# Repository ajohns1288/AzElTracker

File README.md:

# AzElTracker
Arduino firmware to control https://www.thingiverse.com/thing:4664558, designed by jbyrns

This project started as a class project and was designed to be compatible (enough) to work with gPredict/rotctrld. It seems to run pretty well.

## Items Needed
1x Arduino Nano or equivalent

2x A4988 Stepper Boards

2x Stepper Motors

1x Small Magnet

1x Hall effect switch

## How it works
1: At startup, the azimuth is assumed to be due north (0deg) and the elevation runs a homing routine

2: Once homed, serial port is polled for commands from external program.

3: Rotors can be moved indepentently as well as together. Each can rotate continously or to a set position.

See section below for implemented commands

## Hardware adaptation

Since different people might want to use the same logic but for different hardware, the hardware specific values are in the rotorParams.h file. This way, you can tailor the code to your specific application without having to change mulitple variables all over the place

## Commands
Command enumerations based on GS232 Protocol; works with 'rotctld -m 606 -r /dev/xxx' on RaspPi

CMD_R 'R' - Move right continously

CMD_L 'L' - Move left continously

CMD_U 'U' - Move up continously

CMD_D 'D' - Move down continously

CMD_STOP 'S' - Stop all axes

CMD_STOP_AZ 'A' - Stop azimuth only

CMD_STOP_EL 'E' - Stop elevation only

CMD_SPEED 'X' - Xs - Set speed to x (Azimuth only, 4: fast 1: slow)

CMD_MOVETO_AZ 'M' - Mxxx  - Moves to azimuth xxx

CMD_MOVETO 'W' - Wxxx yyy - Moves to azimuth xxx, elevation yyy

CMD_GET_AZ 'C' - Display azimuth position only (NOTE: C2 will display both axes)

CMD_GET_EL 'B' - Display elevation position only

//Non-Standard GS232 Commands

CMD_DEBUG 'Q' - Displays current positions/status/modes of rotor

CMD_SET_HOME 'F' - Unimplmented, may be used to set current position as home in future release

## Drawbacks
Stepper motors do not have feedback. If the motor stalls or skips, your position will be off

## Future Work
Implement compass/accelerometer as position sensor input.

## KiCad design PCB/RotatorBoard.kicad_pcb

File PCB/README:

KiCad files for control board PCB

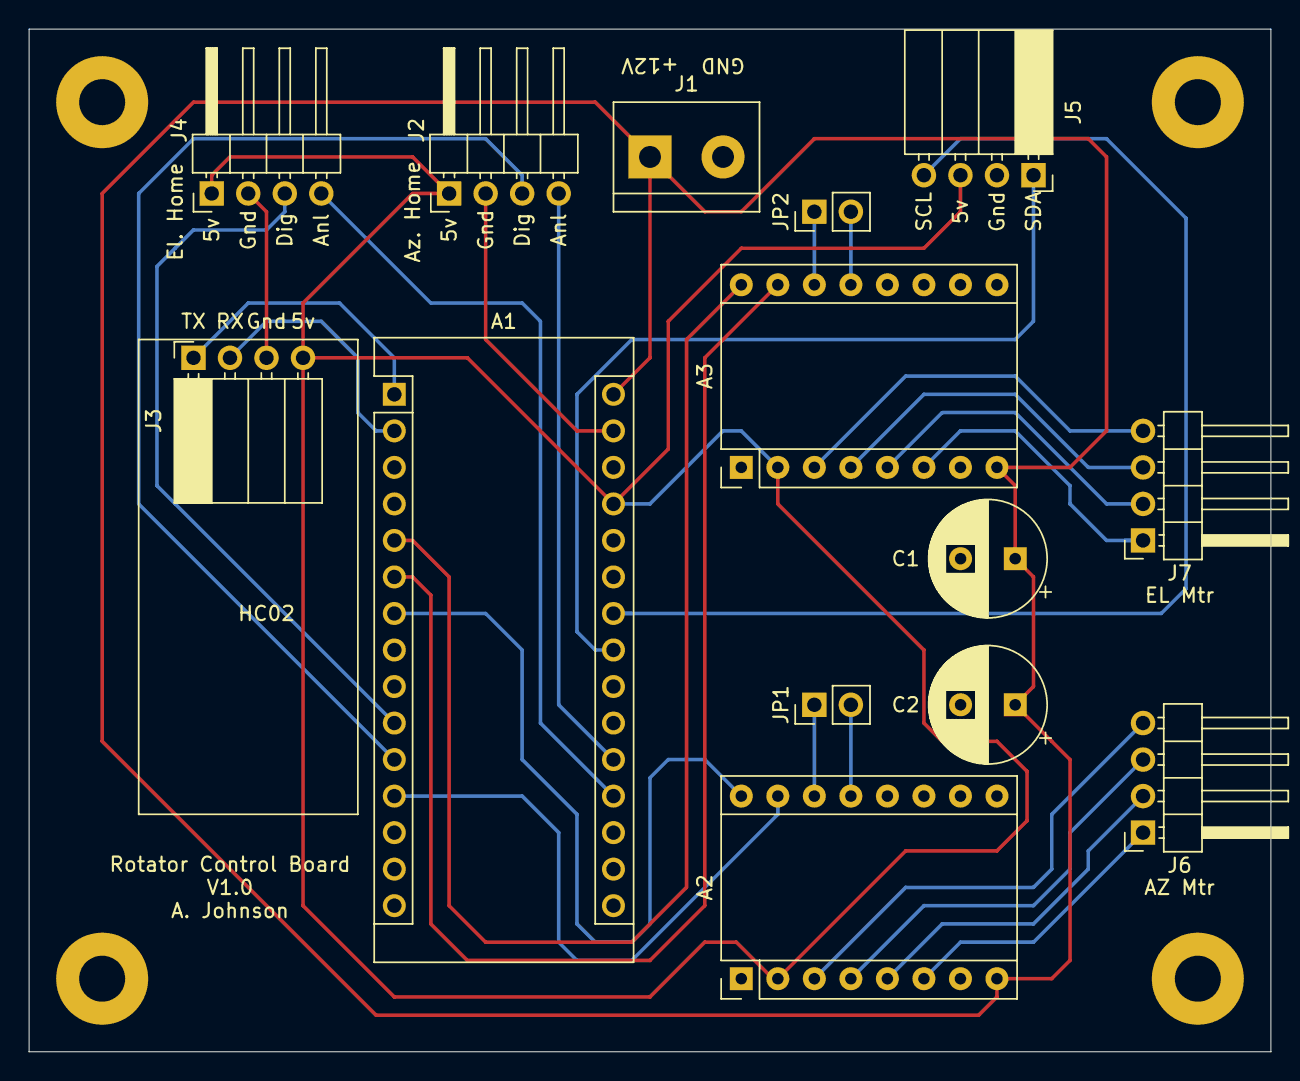
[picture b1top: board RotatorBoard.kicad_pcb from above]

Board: 2 copper layers, 86.4 x 71.1 mm, 14 parts (0 on the bottom side), 27 nets.

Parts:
A1: Arduino_Nano_v3.x; Arduino_Nano
A2, A3: Pololu_Breakout_A4988; Pololu_Breakout-16_15.2x20.3mm
C1, C2: CP1; CP_Radial_D8.0mm_P3.80mm
J1: Screw_Terminal_01x02; TerminalBlock_bornier-2_P5.08mm
J2, J4: Conn_01x04_Male; PinHeader_1x04_P2.54mm_Horizontal
J3, J5: Conn_01x04_Female; PinSocket_1x04_P2.54mm_Horizontal
J6, J7: Conn_01x04_Male; PinHeader_1x04_P2.54mm_HorizontalFlipped
JP1, JP2: Jumper_2_Open; PinHeader_1x02_P2.54mm_Vertical

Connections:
+5V: A1.27, A2.2, A3.2, J2.1, J3.4, J4.1, J5.3
+12V: A1.30, A2.8, A3.8, C1.1, C2.1, J1.1
AZ_DIR: A1.7, A2.16
AZ_HOME_ANL: A1.20, J2.4
AZ_HOME_DIG: A1.11, J2.3
AZ_STEP: A1.12, A2.15
EL_DIR: A1.5, A3.16
EL_HOME_ANL: A1.19, J4.4
EL_HOME_DIG: A1.10, J4.3
EL_STEP: A1.6, A3.15
GND: A1.4, A1.29, A2.1, A2.7, A3.1, A3.7, C1.2, C2.2, J1.2, J2.2, J3.3, J4.2, J5.2
I2C_SCL: A1.24, J5.4
I2C_SDA: A1.23, J5.1
unnamed: A2.3, J6.4
unnamed: A2.4, J6.3
unnamed: A2.5, J6.2
unnamed: A2.6, J6.1
unnamed: A2.13, JP1.2
unnamed: A2.14, JP1.1
unnamed: A3.3, J7.4
unnamed: A3.4, J7.3
unnamed: A3.5, J7.2
unnamed: A3.6, J7.1
unnamed: A3.13, JP2.2
unnamed: A3.14, JP2.1
UART_RX: A1.2, J3.2
UART_TX: A1.1, J3.1

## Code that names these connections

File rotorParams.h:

/*
 * These are the only things you should have to change for using it on your own design
 *
 * To determine the degrees per step, take the degrees per step for the motor (usually 1.8 degrees for a 200 step/rev
 * motor) and multiply it by the gear ratio. In my case, it was 1.8*(1/4.1) which gives 0.43 steps per degree.
 * To avoid floats, the code uses hundredths of degrees (ie 1 degree would be 100).
 */

#ifndef _ROTORPARAM_H
#define _ROTORPARAM_H

//Change these to match your specific rotor/steppers
//To avoid floats this is in 100th of a degree (deg*100)
#define AZ_DEG_PER_STEP 43 //(deg*100)
#define EL_DEG_PER_STEP 6 //(deg*100)

//Currently not used, however this is simply 1/(x/100) of the above
#define AZ_STEPS_PER_DEG 2.389
#define EL_STEPS_PER_DEG 16.66



//Change these to match your electrical setup
#define AZ_STEP_PIN 9
#define AZ_DIR_PIN 4

#define EL_STEP_PIN 3
#define EL_DIR_PIN 2

#define EL_HOME_PIN_DIG 7 //Digital home pin
#define EL_HOME_PIN_ANL A0 //Analog home pin

#define AZ_HOME_PIN_DIG 8  //Digital home pin
#define AZ_HOME_PIN_ANL A1 //Analog home pin

#define INVERT_DIG_HOME 0 //0: Home switch high when at home, 1: Home switch low when at home
#define ANALOG_HOME_VAL 700 // A2D value above which the sensor is considered at home

#define POS_HYST 80 //Hysteresis (deg*100)
#define HOME_MAX_MOVEMENT 7000 //Maximum movement during homing (deg*100)

//For future development
#define USE_ACCEL_4_ELE 0 //Use i2c accelerometer for elevation
#define USE_COMP_4_AZI 0 //Use i2c compass for azimuth


//home


#endif

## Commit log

2021-12-08 Add files via upload
    Initial Publication
2021-12-08 Create LICENSE
2022-01-28 Update finalRotorPort.ino
    Changed hardcoded A0 to use the defined value from header file.
2022-01-29 Update rotor.cpp
    formatting updates
2022-03-12 Documentation update
